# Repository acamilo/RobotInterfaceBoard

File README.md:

### Robot Interface Board

The Robot Interface Board (RIB) is a breakout board for the [ESP32-DevKitC Arduino module](https://www.digikey.com/product-detail/en/espressif-systems/ESP32-DEVKITC-32D-F/1965-1003-ND/9693290). The Dev Kit C is a reference design of the ESP32-WROOM-32 module which houses the WiFi and bluetooth Antenae. The ESP32-WROOM-32 module houses an ESP32 microcontroller. 

#### Datasheet

[Arduino compatiple DevkitC]( https://esp-idf.readthedocs.io/en/latest/get-started/get-started-devkitc.html)

[ESP32 Microcontroller]( https://www.espressif.com/sites/default/files/documentation/esp32_datasheet_en.pdf)

[ESP32-DevKitC Arduino module wireing diagram ](https://dl.espressif.com/dl/schematics/esp32_devkitc_v4-sch-20180607a.pdf)

## PCB

## ESP32Dev Board PINMAP

## IO Pin counts

There are 16 I/O pins availible for use in your programs with no external perpheral already using them.

There are 21 I/O pins availible for use in your programs including the 5 output only strapping pins.

There are 27 I/O pins availible for use in your programs by reusing the boot button pin, serial pins and i2c pins for other purposes. 

## User Button

There is a button connected to pin 0 and is accessible to the users code as a button. If you hold it whild pressing the reset button, however, it will hold the chip in bootloader mode and it will not run your code until the core is reset or programmed over the USB. Once your code starts, this button is availible for use as a button in your code and pressing it will not effect the opperation of the core after your program has started.  

## Pins to Never Use because they will disrupt programming and opperation:

6-11    - These pins are hookups for external system flash and are used by the system flash. Unless you are extending the chips flash capibilities, do not use these. 

1 and 3 -  these are used to program the device and are serial port pins.

## Output Only Pins 

These pins are strapping pins for the core, if pulled to a different state than the default not boot.

These are strapping pins and have to be in known states at the time of the chip booting. If you use them as outputs, be careful to note the the pull up or down resistor states for each. When using these pins make sure the weak-pull resistor will not interfeare with your intended opperation, and do not add additional weak-pull resistors.

```
2  (pull down)
5  (pull up)
12 (pull down)
13 (pull up)
15 (pull up)
```
## Input Only pins

34-39 are input only. They have no output modes at all. Analog input and digital input are availible.

```
35
34
39
36
```

## Availible as Both Input and Output

```
4
14
16-19
21-23
25-27
32-33
```
## External Use pins

0 is the boot pin, if held low during a reset it will prevent the device from booting

1 and 3 are the serial port used for programming and print statements. This should not be used for user functions, but can be used if serial functionality is needed.

13 Has an LED connected to it on the RIB

22 and 21 have 4.7kOhm pullups on them and are connected to the Wii accessory port. These can be used with other i2c devices.
See: https://github.com/acamilo/RobotInterfaceBoard/issues/31

27 Is connected to the Wii header as controller detect. When the controller is connected, this is pulled to 3.3v. It is open when the controller is not connected.  

## Availible Servo/PWM/AnalogWrite Pins

The ESP32 can generate up to 16 simultanious Servo signels. 

```
4     
5    
12-19 
21-23 
25-27 
32-33 
```

### Timer distribution for PWM
The ESP32 has 4 timers availible for use in PWM generation. All PWM channels using a given timer have the same base frequency. Changing the frequency of a channel will change the frequency of other channels. Note the chart for how the PWM channel allocations coorospond to timers:

```
/*
 * LEDC Chan to Group/Channel/Timer Mapping
** ledc: 0  => Group: 0, Channel: 0, Timer: 0
** ledc: 1  => Group: 0, Channel: 1, Timer: 0
** ledc: 2  => Group: 0, Channel: 2, Timer: 1
** ledc: 3  => Group: 0, Channel: 3, Timer: 1
** ledc: 4  => Group: 0, Channel: 4, Timer: 2
** ledc: 5  => Group: 0, Channel: 5, Timer: 2
** ledc: 6  => Group: 0, Channel: 6, Timer: 3
** ledc: 7  => Group: 0, Channel: 7, Timer: 3
** ledc: 8  => Group: 1, Channel: 0, Timer: 0
** ledc: 9  => Group: 1, Channel: 1, Timer: 0
** ledc: 10 => Group: 1, Channel: 2, Timer: 1
** ledc: 11 => Group: 1, Channel: 3, Timer: 1
** ledc: 12 => Group: 1, Channel: 4, Timer: 2
** ledc: 13 => Group: 1, Channel: 5, Timer: 2
** ledc: 14 => Group: 1, Channel: 6, Timer: 3
** ledc: 15 => Group: 1, Channel: 7, Timer: 3
*/
```

When using ESP32PWM objects, changing the frequency will check for timer cross-talk. If you re-set the frequency of a PWM indirectly, the object will print this warning:

```
	WARNING PWM channel 1 shares a timer with 0
	changing the frequency to 330.00 Hz will ALSO change channel 0 
	from its previous frequency of 50.00 Hz
```

If you get this warning you can space out the attach events of the hardware using ESP32PWM using dummy objects. To consume a channel without activating a pwm, you can add this to your code between attach method calls. 

```
ESP32PWM dummy;
dummy.getChannel();
```
## Availible DAC pins
```
25
26
```
These pins when used with analogWrite will produce an 8 bit analog value on the given pin. The value is from 0-3.3v mapped to 0-255 values. The api is to simply use analogWrite().

## Interrupt

For code examples: https://techtutorialsx.com/2017/09/30/esp32-arduino-external-interrupts/

Availible interruptable pins are all input pins.

# Development Computer Options  

## Option 1) A lab machine

Availible to all students. 

Note that the driver is installed on these computers

Note that Arduino with the ESP32 toolchain is already installed in C:\WPIAPPS\arduino-1.8.3\

Note Eclipse is installed on all workstations with the Sloeber plugin installed. 

##  Option 2) Personal Machine

### Supported for this class

Windows 10 Pro 

A user name with no " " in the file path. Generally it is safe to use your WPI username as the username on your computer.

Fresh install is genearlly reccomended every 6 months. Install disk are availible to students as a resource from the WPI Helpdesk.

OneDrive and Dropbox conflict with the install process and must be fully removed from the user file paths. 

Eclipse should be installed in 

```
C:/eclipse
```

Arduino should be installed in 

```
C:/RBE-arduino-install/
```

After installation of both, ensure your user has write access to the directories. 

### Unsupported OS's

MacOS is unsupported and only intermittantly working. Drivers have been an issue with programming our board, and virtualization of Windows within OSX is tested non-working. If you have Mac OSX please install a fresh copy of Windows 10 nativly and dual boot. 

Ubuntu 16.04 is unsupported but works well.

Ubuntu 18.04 is unsupported but works well with some creative directions following. This will take more effort and would require pre-existing proficency in Linux. If you have 18.04 please install Windows 10 or 16.04. 

### How to get Windows 10 as a Student for free from WPI

To get your student copy of Windows go here: 

https://onlinestore.wpi.edu/

Select windows 10, and download it. For students you get one copy and it is free. 

You can follow this tutorial to install it:

https://www.youtube.com/watch?v=aTVOTY93XXU

# Arduino and the ESP32 Toolchain

This is installed on the lab machines already. 

After extracting the Zip file, install the 64 bit version of the driver. 

https://www.silabs.com/products/development-tools/software/usb-to-uart-bridge-vcp-drivers

Arduino IDE download :

https://github.com/WPIRoboticsEngineering/RobotInterfaceBoard/releases/download/rev5-1/RBE-arduino110718.zip

And extract it on your computer in 

```
C:/RBE-arduino-install/
```

Make a sketchbook folder in C:/, or (R:/ on the lab machines) make a folder:

```
C:/RBEArduino/
```

Make sure it is user level read-write

Run Arduino in the extracted folder.

Open the Preferences in Arduino and set the Sketchbook location to:

```
C:/RBEArduino/
```
Use [Arduino IDE and Github Desktop](https://github.com/WPIRoboticsEngineering/RobotInterfaceBoard/blob/master/UseArduinoGithubDesktop.md)

After your Arduino is installed and the ESP32 toolchain is up and running, open Arduino IDE and Select your board:

```
Tools->Board->ESP32 Dev Module
```

And select your port:

```
Tools->Port-> (the port that your arduino is connected to)
```

## Personal Computer install Linux / Mac  (Unsupported)

Ubuntu 18.04 Instructions:

[InstallToolchainOnUbuntu18-04.md](InstallToolchainOnUbuntu18-04.md)

Ubuntu 16.04 Instructions:

https://github.com/espressif/arduino-esp32/blob/master/docs/arduino-ide/debian_ubuntu.md

Mac instructions (NOT SUPPORTED BY RBE, HAS LOTS OF PROBLEMS):

https://github.com/espressif/arduino-esp32/blob/master/docs/arduino-ide/mac.md

## Install Eclipse And Setup Eclipse on Personal Machine

 [See Eclipse install instructions in InstallEclipse.md](https://github.com/WPIRoboticsEngineering/RobotInterfaceBoard/blob/master/InstallEclipse.md)
 
 [Open Projects in Eclipse using the Eclipse instructions](https://github.com/WPIRoboticsEngineering/RobotInterfaceBoard/blob/master/UseEclipse.md)

# Arduino Libraries
## HOWTO
For detailed instructions on how libraries work, see: https://www.arduino.cc/en/Guide/Libraries

Open Arduino and select Sketch->Libraries -> Manage Libraries
## Which Libraries

### 1001

ESP32Servo

ESP32Encoder

### 2001
Search for and install:

ESP32Servo

ESP32Encoder

Esp32SimplePacketComs

SimplePacketComs

### 2002
Search for and install:

ESP32Servo

ESP32Encoder

Adafruit_BNO055

Adafruit Unified Sensor

Esp32SimplePacketComs

SimplePacketComs

DFRobotIRPosition

# FAQ and troubleshooting

### "I dont see 'ESP32 Dev Module' as an option in Arduino when I try to select my board..."

* Use a lab machine. This will not be a problem on the lab machines. 

* You need to install the ESP 32 toolchain. See https://github.com/WPIRoboticsEngineering/RobotInterfaceBoard#personal-computer-install-windows--supported

### "I can compile the code but I do not have a serial port option in Arduino..."

* Ensure the driver installed https://github.com/WPIRoboticsEngineering/RobotInterfaceBoard#personal-computer-install-windows--supported

* If its a MAC, this is the issue that causes us to say MacOS is UNSUPPORTED. Install Windows https://github.com/WPIRoboticsEngineering/RobotInterfaceBoard#how-to-get-windows-10-as-a-student-for-free-from-wpi

* Make sure the USB Micro cable is a data cable, not just a crappy USB charging cable with no data lines. 

### "I can select the correct serial port, put it wont program or times out while programming..."

* Program an example script using Lab computer   (if this works have them re-download the pre-packaged arduino from https://github.com/WPIRoboticsEngineering/RobotInterfaceBoard#personal-computer-install-windows--supported ) 

* Is the serial moniter open? Close it and try again. 

* Did it program earlier? Unplug the USB and plug it back in.

* Hold Boot button and Strobe the enable button to set core into bootloader mode. Try to program. (If this helps, you are printing too much data to the serial port)

* Unplug everything from all IO (If this fixes it, check the pins and voltages, also check for diode dead-shorts check https://github.com/WPIRoboticsEngineering/RobotInterfaceBoard#pins-to-never-use )

* Check to see if the processor or regulator is HOT. If it is, a dead-short or over-voltage event occured and the device is dead forever. Replace. 

### "I can program it but it but it keeps rebooting over and over..."

* Null pointers are the #1 cause of this behavior, use print statements to isolate the point where it reboots and check for null pointers. This is the issue 9 out of 10 times. 

* Interrupt issues - Interrupts that access memory that is used by non-interrupt code without a mutex or semiphore. Try disabling the interrupt and if this fixed the reboot issue, then go ahead and implement the mutex locking. 

* Something may also be plugged into one of the off-limits pins, or your code is reconfiguring and messing up one of these pins. See: https://github.com/WPIRoboticsEngineering/RobotInterfaceBoard#pins-to-never-use 

### "This processor seems more complicated than the Uno and the Mega, why are we using it?"

* The ESP32 is a faster core at 260Mhz, vs the 16Mhz Uno. It is also dual-core.

* It has more perpherals needed for building robots, 16x 12 bit ADC, 2x DAC and 16 hardware encoder perpherals

* It has hardware and software that support WiFi for communications. 

* 32 bit processing with an FPU means complex math is possible on the microcontroller. 

* It is Arduino compatible for programming and Library support

* It is an open source design of the DevKit-C module, using an open source MIPS core and open soruce tool-chain

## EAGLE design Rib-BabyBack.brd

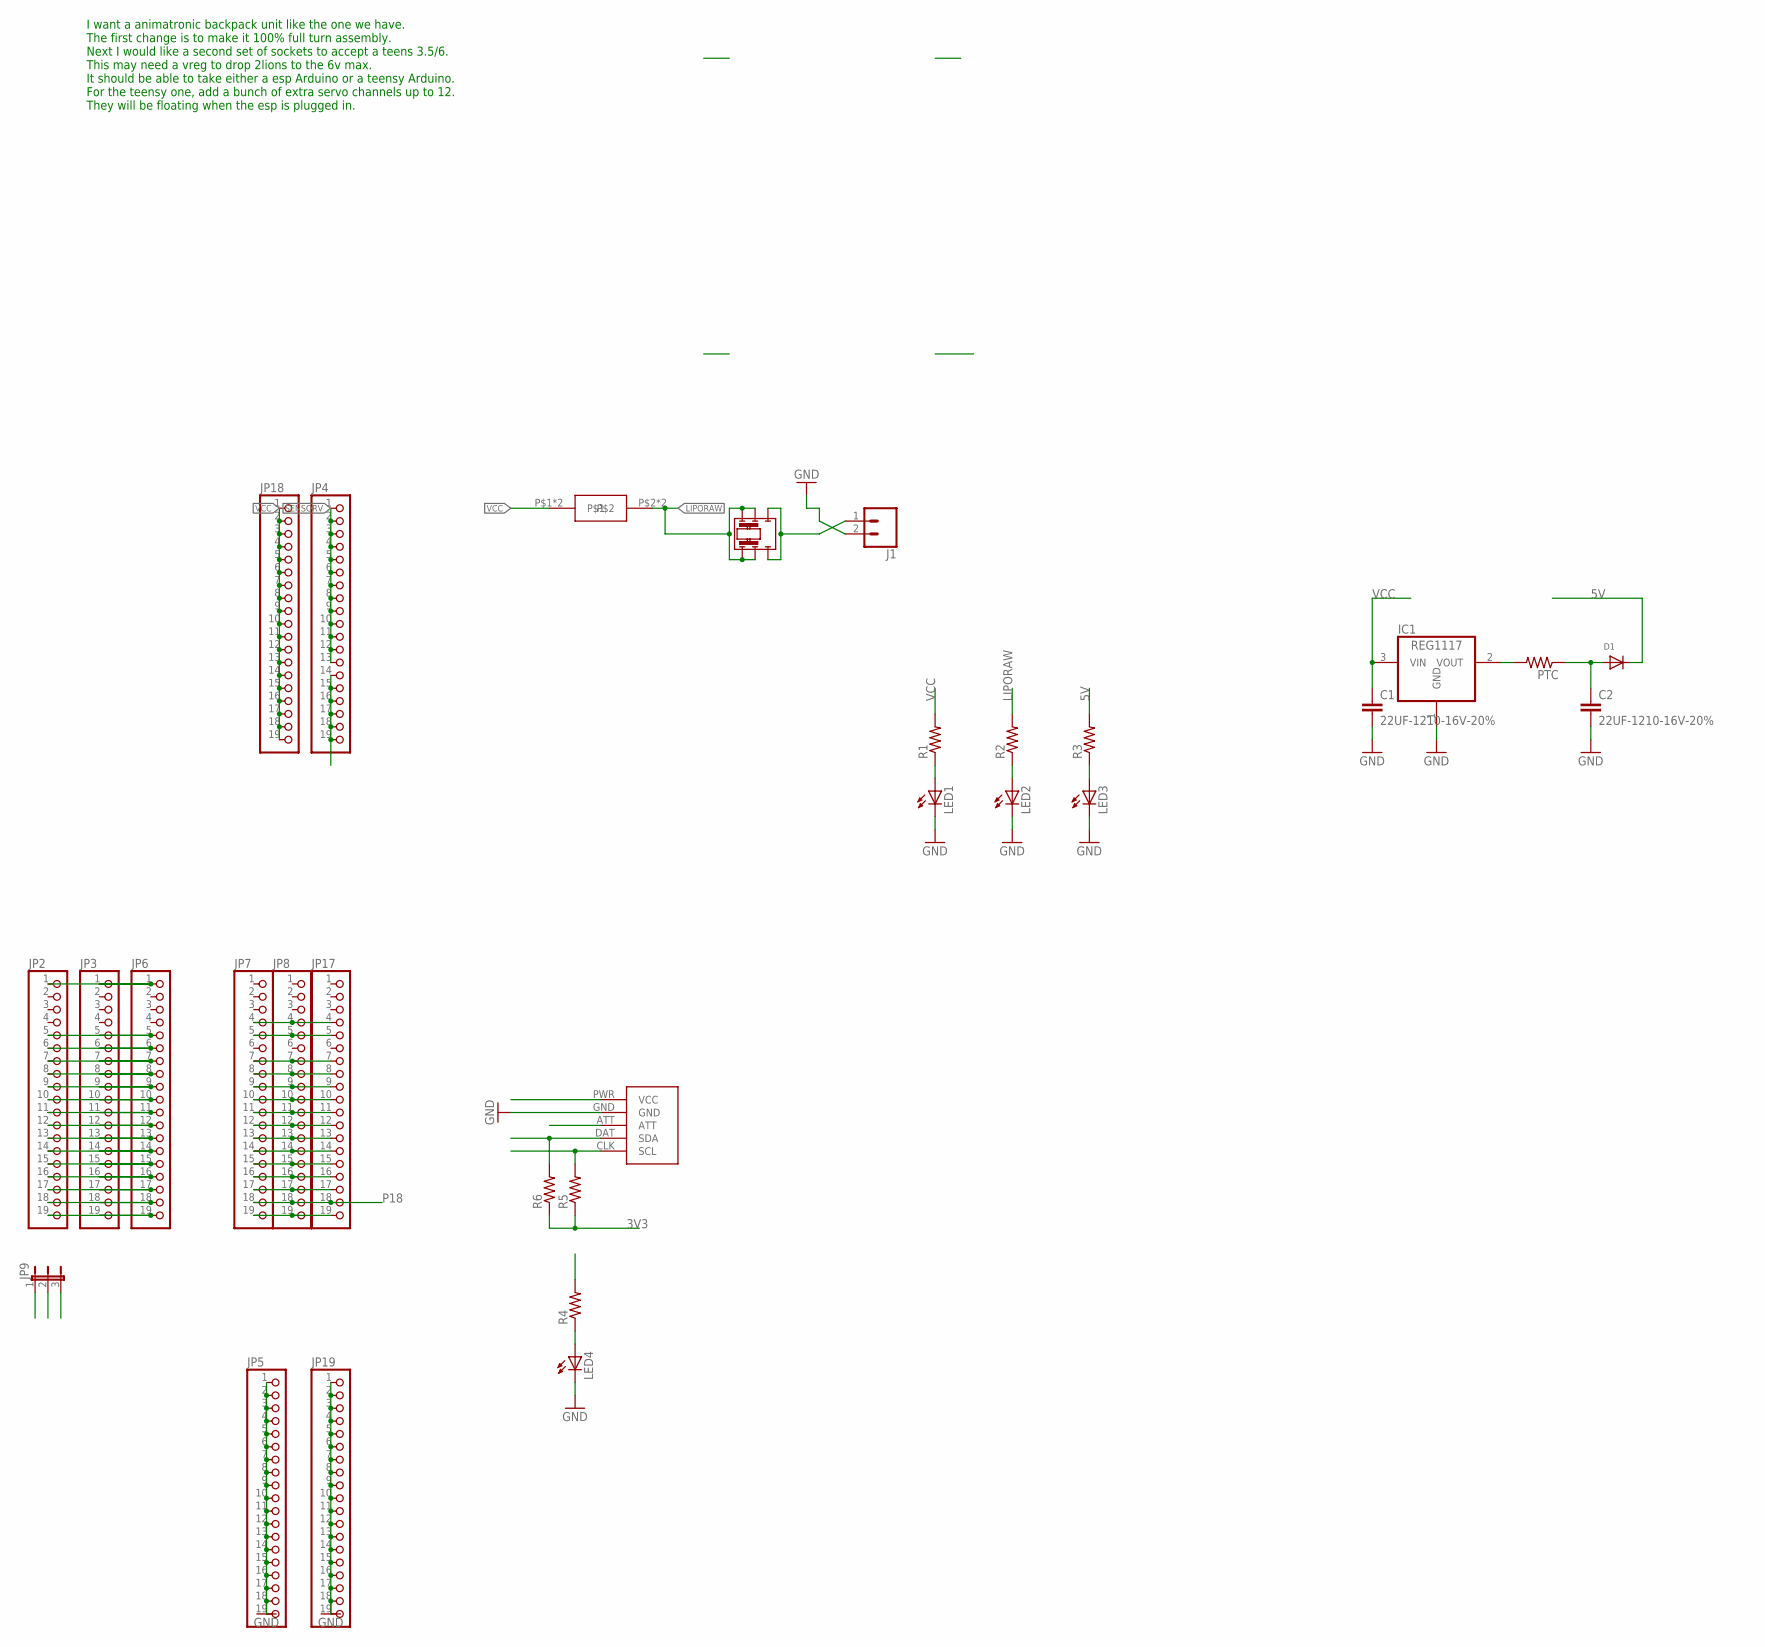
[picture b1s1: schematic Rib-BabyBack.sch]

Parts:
C1, C2: 22UF-1210-16V-20%; 1210
D1: DIODESOD-523; SOD-523
F4: 3557-2
IC1: REG1117; SOT223
J1: CONN_023.5MM_LOCK; SCREWTERMINAL-3.5MM-2_LOCK
JP2, JP3, JP4, JP5, JP6, JP7, JP8, JP17, JP18, JP19: PINHD-1X19; 1X19
JP9: JP2E; JP2
LED1, LED2, LED3, LED4: LED_ESML0603; LED_SML0603
PTC: R-US_R0805; R0805
R1, R2, R3, R4, R5, R6: R-US_R0603; R0603
SW1: DPDT; GF-126-0327
U$5: WIICHUCK; CHUCK

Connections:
3V3: JP2.19, JP3.19, JP6.19, JP9.1, R5.1, R6.1, U$5.PWR (VCC)
DET: JP2.9, JP3.9, JP6.9, U$5.ATT
GND: C1.2, C2.2, IC1.1 (GND), J1.2, JP2.6, JP3.6, JP5.1, JP5.2, JP5.3, JP5.4, JP5.5, JP5.6, JP5.7, JP5.8, JP5.9, JP5.10, JP5.11, JP5.12, JP5.13, JP5.14, JP5.15, JP5.16, JP5.17, JP5.18, JP5.19, JP6.6, JP7.13, JP7.19, JP8.13, JP8.19, JP17.13, JP17.19, JP19.1, JP19.2, JP19.3, JP19.4, JP19.5, JP19.6, JP19.7, JP19.8, JP19.9, JP19.10, JP19.11, JP19.12, JP19.13, JP19.14, JP19.15, JP19.16, JP19.17, JP19.18, JP19.19, LED1.C, LED2.C, LED3.C, LED4.C, U$5.GND
LIPORAW: F4.P$2, F4.P$3, R2.2, SW1.A1, SW1.A2, SW1.B1, SW1.B2
unnamed: LED4.A, R4.1
unnamed: C2.1, D1.A, PTC.1
unnamed: IC1.2 (VOUT), PTC.2
unnamed: J1.1, SW1.C1, SW1.C2
unnamed: JP2.7, JP3.7, JP6.7
unnamed: JP2.8, JP3.8, JP6.8
unnamed: JP2.10, JP3.10, JP6.10
unnamed: JP2.11, JP3.11, JP6.11
unnamed: JP2.12, JP3.12, JP6.12
unnamed: JP2.13, JP3.13, JP6.13
unnamed: JP2.14, JP3.14, JP6.14
unnamed: JP2.15, JP3.15, JP6.15
unnamed: JP2.16, JP3.16, JP6.16
unnamed: JP2.17, JP3.17, JP6.17
unnamed: JP2.18, JP3.18, JP6.18
unnamed: LED1.A, R1.1
unnamed: JP7.4, JP8.4, JP17.4
unnamed: JP7.5, JP8.5, JP17.5
unnamed: JP7.7, JP8.7, JP17.7
unnamed: JP7.8, JP8.8, JP17.8
unnamed: JP7.9, JP8.9, JP17.9
unnamed: JP7.10, JP8.10, JP17.10
unnamed: JP7.11, JP8.11, JP17.11
unnamed: JP7.12, JP8.12, JP17.12
unnamed: LED2.A, R2.1
unnamed: LED3.A, R3.1
P13: JP2.5, JP3.5, JP6.5, R4.2
P18: JP7.18, JP8.18, JP17.18
RX0: JP7.15, JP8.15, JP17.15
SCL: JP7.17, JP8.17, JP17.17, R5.2, U$5.CLK (SCL)
SDA: JP7.14, JP8.14, JP17.14, R6.2, U$5.DAT (SDA)
TX0: JP7.16, JP8.16, JP17.16
VCC: C1.1, F4.P$1, F4.P$4, IC1.3 (VIN), JP18.1, JP18.2, JP18.3, JP18.4, JP18.5, JP18.6, JP18.7, JP18.8, JP18.9, JP18.10, JP18.11, JP18.12, JP18.13, JP18.14, JP18.15, JP18.16, JP18.17, JP18.18, JP18.19, R1.2

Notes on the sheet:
I want a animatronic backpack unit like the one we have. The first change is to make it 100% full turn assembly. Next I would like a second set of sockets to accept a teens 3.5/6. This may need a vreg to drop 2lions to the 6v max. It should be able to take either a esp Arduino or a teensy Arduino. 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

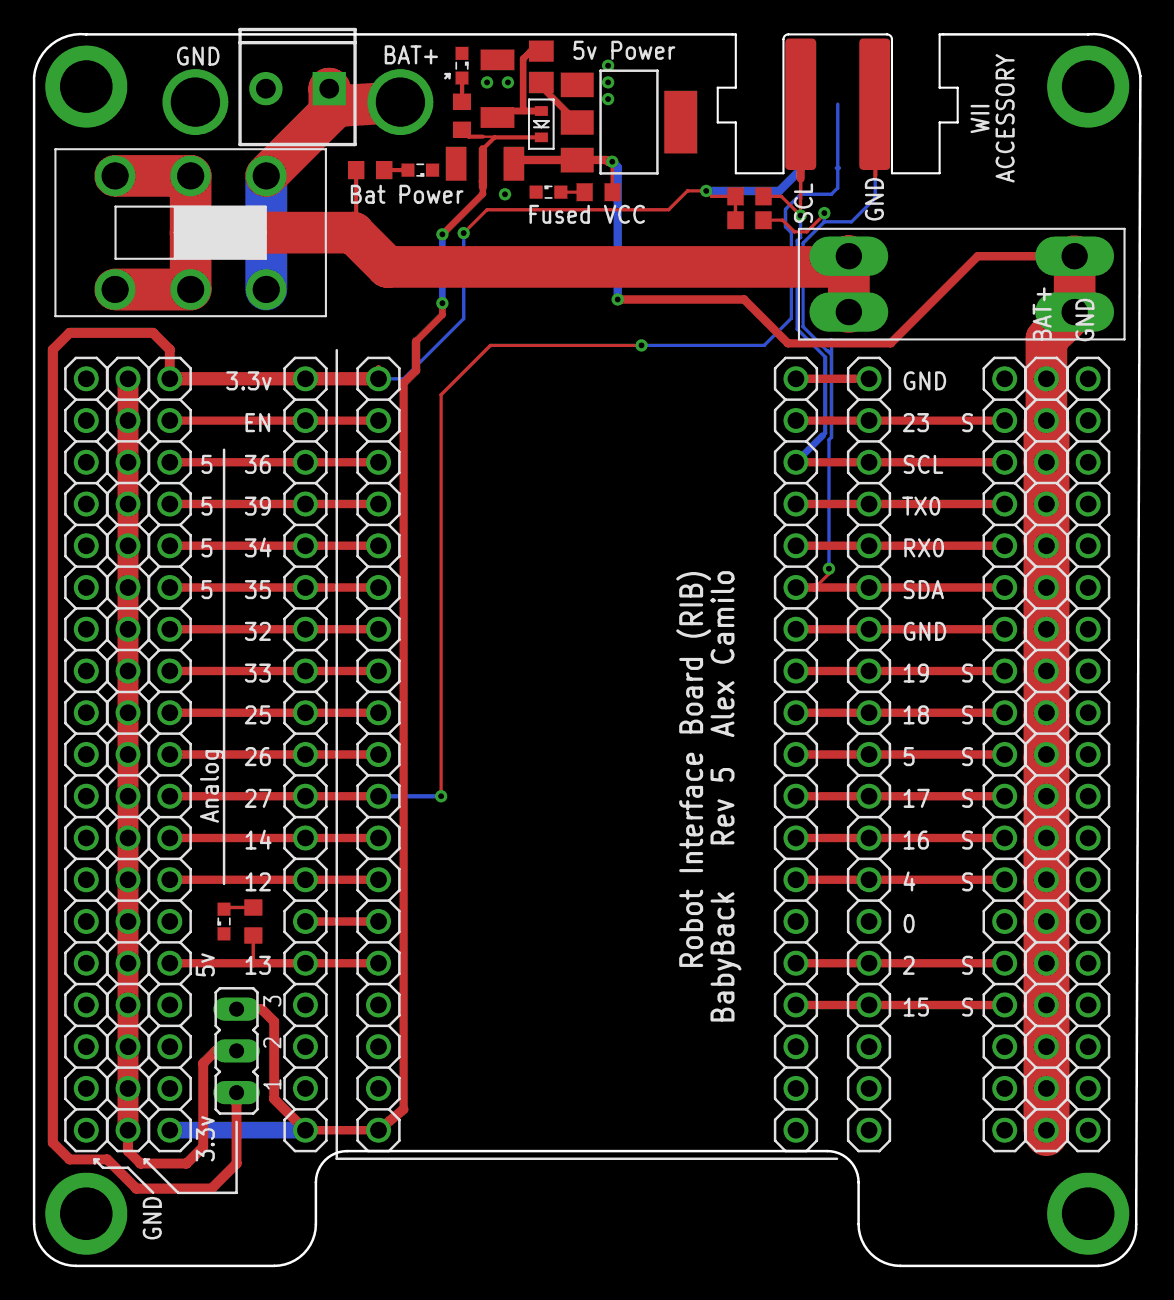
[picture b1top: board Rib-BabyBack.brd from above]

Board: 2 copper layers, 67.3 x 74.9 mm, 30 parts (0 on the bottom side), 39 nets.

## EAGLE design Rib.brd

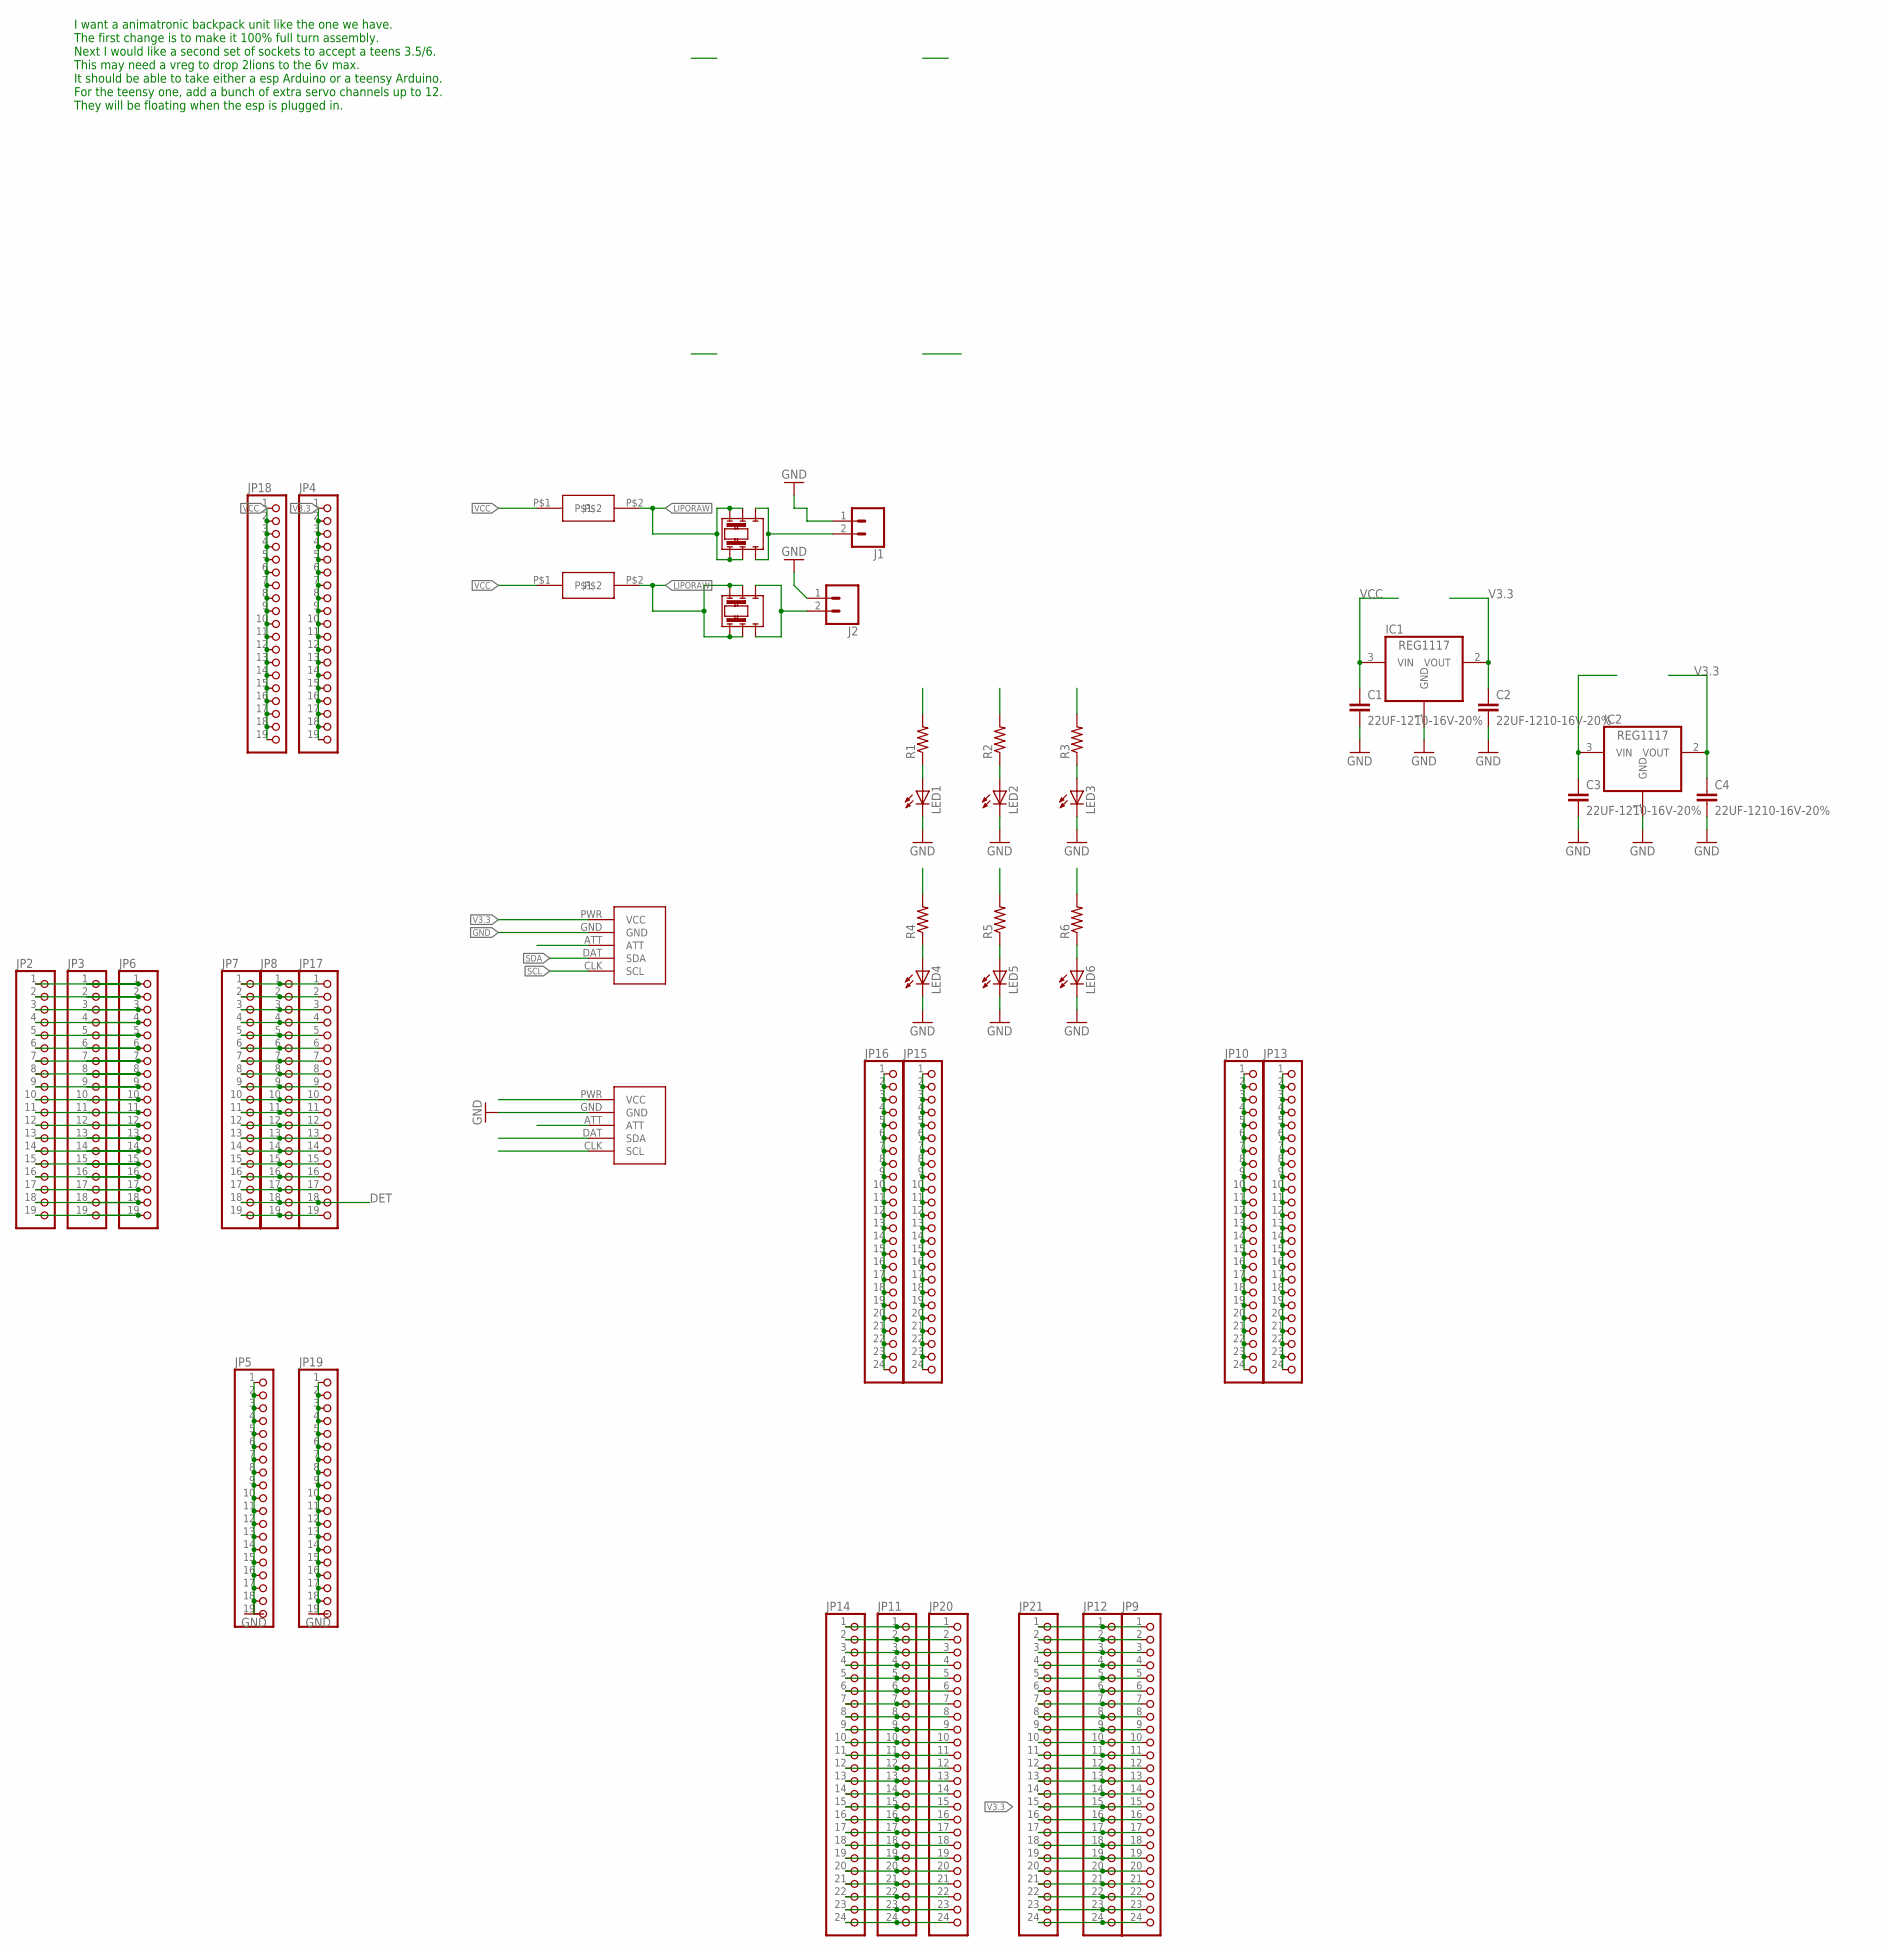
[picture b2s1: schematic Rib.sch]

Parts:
C1, C2, C3, C4: 22UF-1210-16V-20%; 1210
F3, F4: 3557-2
IC1, IC2: REG1117; SOT223
J1, J2: CONN_023.5MM_LOCK; SCREWTERMINAL-3.5MM-2_LOCK
JP2, JP3, JP4, JP5, JP6, JP7, JP8, JP17, JP18, JP19: PINHD-1X19; 1X19
JP9, JP10, JP11, JP12, JP13, JP14, JP15, JP16, JP20, JP21: PINHD-1X24; 1X24
LED1, LED2, LED3, LED4, LED5, LED6: LED_ESML0603; LED_SML0603
R1, R2, R3, R4, R5, R6: R-US_R0603; R0603
SW1, SW2: DPDT; GF-126-0327
U$3, U$5: WIICHUCK; CHUCK

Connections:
5V: JP2.1, JP3.1, JP6.1, JP11.1, JP14.1, JP20.1
DET: JP7.18, JP8.18, JP9.24, JP12.24, JP17.18, JP21.24, U$3.ATT, U$5.ATT
GND: C1.2, C2.2, C3.2, C4.2, IC1.1 (GND), IC2.1 (GND), J1.1, J2.1, JP2.6, JP3.6, JP5.1, JP5.2, JP5.3, JP5.4, JP5.5, JP5.6, JP5.7, JP5.8, JP5.9, JP5.10, JP5.11, JP5.12, JP5.13, JP5.14, JP5.15, JP5.16, JP5.17, JP5.18, JP5.19, JP6.6, JP7.13, JP7.19, JP8.13, JP8.19, JP9.1, JP11.2, JP11.15, JP12.1, JP13.1, JP13.2, JP13.3, JP13.4, JP13.5, JP13.6, JP13.7, JP13.8, JP13.9, JP13.10, JP13.11, JP13.12, JP13.13, JP13.14, JP13.15, JP13.16, JP13.17, JP13.18, JP13.19, JP13.20, JP13.21, JP13.22, JP13.23, JP13.24, JP14.2, JP14.15, JP16.1, JP16.2, JP16.3, JP16.4, JP16.5, JP16.6, JP16.7, JP16.8, JP16.9, JP16.10, JP16.11, JP16.12, JP16.13, JP16.14, JP16.15, JP16.16, JP16.17, JP16.18, JP16.19, JP16.20, JP16.21, JP16.22, JP16.23, JP16.24, JP17.13, JP17.19, JP19.1, JP19.2, JP19.3, JP19.4, JP19.5, JP19.6, JP19.7, JP19.8, JP19.9, JP19.10, JP19.11, JP19.12, JP19.13, JP19.14, JP19.15, JP19.16, JP19.17, JP19.18, JP19.19, JP20.2, JP20.15, JP21.1, LED1.C, LED2.C, LED3.C, LED4.C, LED5.C, LED6.C, U$3.GND, U$5.GND
LIPORAW: F3.P$2, F4.P$2, R2.2, R5.2, SW1.A1, SW1.A2, SW1.B1, SW1.B2, SW2.A1, SW2.A2, SW2.B1, SW2.B2
unnamed: JP11.23, JP14.23, JP20.23
unnamed: JP11.24, JP14.24, JP20.24
unnamed: JP2.2, JP3.2, JP6.2
unnamed: JP2.3, JP3.3, JP6.3
unnamed: JP2.4, JP3.4, JP6.4
unnamed: JP2.5, JP3.5, JP6.5
unnamed: J1.2, SW1.C1, SW1.C2
unnamed: JP2.7, JP3.7, JP6.7
unnamed: JP2.8, JP3.8, JP6.8
unnamed: JP2.9, JP3.9, JP6.9
unnamed: JP2.10, JP3.10, JP6.10
unnamed: JP2.11, JP3.11, JP6.11
unnamed: JP2.12, JP3.12, JP6.12
unnamed: JP2.13, JP3.13, JP6.13
unnamed: JP2.14, JP3.14, JP6.14
unnamed: JP2.15, JP3.15, JP6.15
unnamed: JP2.16, JP3.16, JP6.16
unnamed: JP2.17, JP3.17, JP6.17
unnamed: JP2.18, JP3.18, JP6.18
unnamed: LED1.A, R1.1
unnamed: JP7.1, JP8.1, JP17.1
unnamed: JP7.2, JP8.2, JP17.2
unnamed: JP7.3, JP8.3, JP17.3
unnamed: JP7.4, JP8.4, JP17.4
unnamed: JP7.5, JP8.5, JP17.5
unnamed: JP7.6, JP8.6, JP17.6
unnamed: JP7.7, JP8.7, JP17.7
unnamed: JP7.8, JP8.8, JP17.8
unnamed: JP7.9, JP8.9, JP17.9
unnamed: JP7.10, JP8.10, JP17.10
unnamed: JP7.11, JP8.11, JP17.11
unnamed: JP7.12, JP8.12, JP17.12
unnamed: LED2.A, R2.1
unnamed: LED3.A, R3.1
unnamed: J2.2, SW2.C1, SW2.C2
unnamed: LED4.A, R4.1
unnamed: LED5.A, R5.1
unnamed: LED6.A, R6.1
unnamed: JP11.3, JP14.3, JP20.3
unnamed: JP11.4, JP14.4, JP20.4
unnamed: JP11.5, JP14.5, JP20.5
unnamed: JP11.6, JP14.6, JP20.6
unnamed: JP11.7, JP14.7, JP20.7
unnamed: JP11.10, JP14.10, JP20.10
unnamed: JP11.11, JP14.11, JP20.11
unnamed: JP11.12, JP14.12, JP20.12
unnamed: JP11.13, JP14.13, JP20.13
unnamed: JP11.14, JP14.14, JP20.14
unnamed: JP11.16, JP14.16, JP20.16
unnamed: JP11.17, JP14.17, JP20.17
unnamed: JP11.18, JP14.18, JP20.18
unnamed: JP11.19, JP14.19, JP20.19
unnamed: JP11.20, JP14.20, JP20.20
unnamed: JP11.21, JP14.21, JP20.21
unnamed: JP11.22, JP14.22, JP20.22
unnamed: JP9.2, JP12.2, JP21.2
unnamed: JP9.3, JP12.3, JP21.3
unnamed: JP9.4, JP12.4, JP21.4
unnamed: JP9.5, JP12.5, JP21.5
unnamed: JP9.6, JP12.6, JP21.6
unnamed: JP9.7, JP12.7, JP21.7
unnamed: JP9.8, JP12.8, JP21.8
unnamed: JP9.9, JP12.9, JP21.9
unnamed: JP9.10, JP12.10, JP21.10
unnamed: JP9.13, JP12.13, JP21.13
unnamed: JP9.14, JP12.14, JP21.14
unnamed: JP9.16, JP12.16, JP21.16
unnamed: JP9.17, JP12.17, JP21.17
unnamed: JP9.18, JP12.18, JP21.18
unnamed: JP9.19, JP12.19, JP21.19
unnamed: JP9.20, JP12.20, JP21.20
unnamed: JP9.21, JP12.21, JP21.21
unnamed: JP9.22, JP12.22, JP21.22
unnamed: JP9.23, JP12.23, JP21.23
RX0: JP7.15, JP8.15, JP9.12, JP12.12, JP17.15, JP21.12
SCL: JP7.17, JP8.17, JP11.8, JP14.8, JP17.17, JP20.8, U$3.CLK (SCL), U$5.CLK (SCL)
SDA: JP7.14, JP8.14, JP11.9, JP14.9, JP17.14, JP20.9, U$3.DAT (SDA), U$5.DAT (SDA)
TX0: JP7.16, JP8.16, JP9.11, JP12.11, JP17.16, JP21.11
V3.3: C2.1, C4.1, IC1.2 (VOUT), IC2.2 (VOUT), JP2.19, JP3.19, JP4.1, JP4.2, JP4.3, JP4.4, JP4.5, JP4.6, JP4.7, JP4.8, JP4.9, JP4.10, JP4.11, JP4.12, JP4.13, JP4.14, JP4.15, JP4.16, JP4.17, JP4.18, JP4.19, JP6.19, JP9.15, JP10.1, JP10.2, JP10.3, JP10.4, JP10.5, JP10.6, JP10.7, JP10.8, JP10.9, JP10.10, JP10.11, JP10.12, JP10.13, JP10.14, JP10.15, JP10.16, JP10.17, JP10.18, JP10.19, JP10.20, JP10.21, JP10.22, JP10.23, JP10.24, JP12.15, JP21.15, R3.2, R6.2, U$3.PWR (VCC), U$5.PWR (VCC)
VCC: C1.1, C3.1, F3.P$1, F4.P$1, IC1.3 (VIN), IC2.3 (VIN), JP15.1, JP15.2, JP15.3, JP15.4, JP15.5, JP15.6, JP15.7, JP15.8, JP15.9, JP15.10, JP15.11, JP15.12, JP15.13, JP15.14, JP15.15, JP15.16, JP15.17, JP15.18, JP15.19, JP15.20, JP15.21, JP15.22, JP15.23, JP15.24, JP18.1, JP18.2, JP18.3, JP18.4, JP18.5, JP18.6, JP18.7, JP18.8, JP18.9, JP18.10, JP18.11, JP18.12, JP18.13, JP18.14, JP18.15, JP18.16, JP18.17, JP18.18, JP18.19, R1.2, R4.2

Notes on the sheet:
I want a animatronic backpack unit like the one we have. The first change is to make it 100% full turn assembly. Next I would like a second set of sockets to accept a teens 3.5/6. This may need a vreg to drop 2lions to the 6v max. It should be able to take either a esp Arduino or a teensy Arduino. 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

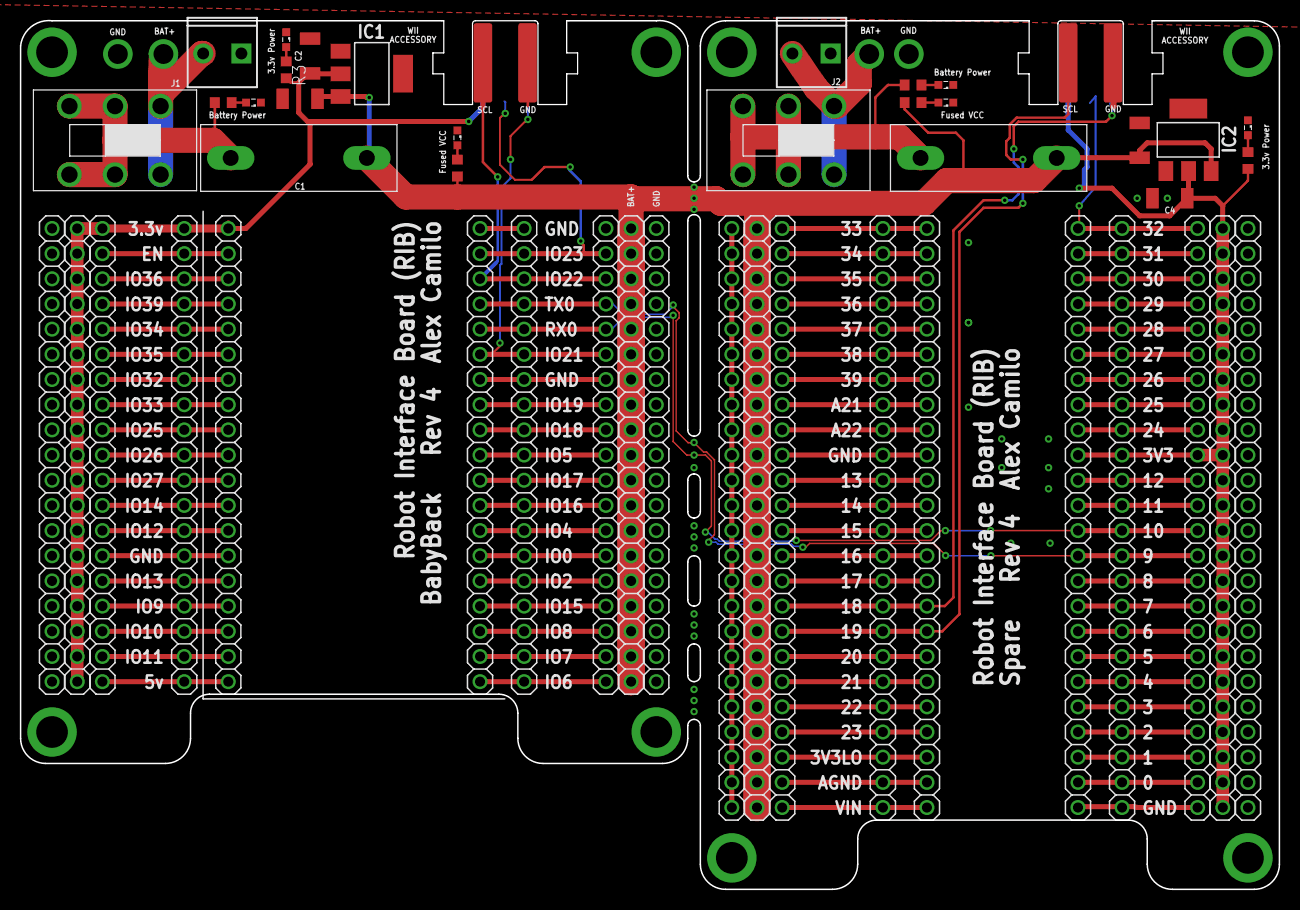
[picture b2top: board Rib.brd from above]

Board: 2 copper layers, 127.0 x 87.6 mm, 46 parts (0 on the bottom side), 84 nets.

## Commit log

2017-11-30 Rev 3 commit
2018-02-15 Updated Locking connecter library footprint with more clearence for locking pins
2018-02-15 Updated PCB footprints with updated wiichuck footprint
2018-02-15 Replaced JST power connectors with screw terminals
2018-02-15 Moved teensy power connector and added solder lugs for a cable to both boards
2018-02-15 ESP32 SDA now on pin 21
2018-02-27 label wii connector pins
2018-02-27 label Power and GND on battery connection
2018-02-27 DET pins routed to esp and teensy
2018-02-27 upped rev no to 4
2018-03-02 BOM and Centroid added
2018-03-02 Gerbers added
2018-03-02 DK parts for all lines
2018-03-22 Replaced fuseholder with blade style automotive fuse
2018-03-22 Added Power, Fuse, Regulated satus LEDs
2018-04-04 #28 Adding a readme
2018-04-04 Adding image
2018-04-12 Issue #35: Split esp32 board off into its own file
2018-04-12 Issue #26 Disconnect specific IO used by System Resources on ESP32
2018-04-12 Issue #32 ESP32 needs a user accessible LED on 13
2018-04-12 Issue #22 Solder lugs resized to 3MM diameter holes and moved
2018-04-12 Issue #19 4k7 ohm pullups to 3.3v are needed on SDA and SCL
2018-04-13 Issue #18 Fix footprint for fuse holder
2018-04-13 Issue #21 Added a pad for a PTC resetabble fuse for the 3.3v rail
2018-04-13 Issues #33 and 4 and #36
2018-04-13 Issue #34
2018-04-20 Resolved issue 37
2018-04-20 Resolved issue 38
2018-04-20 Resolved issue 31
2018-04-26 Resolved issue #24
2018-04-26 Resolved issue #23
2018-04-30 Resolved issue #27
2018-04-30 added board image and readme. #28
2018-04-30 Moving images into folder
2018-05-03 Moved fuse holder as per #40
2018-05-03 Updated silkscreen indicating analog pins #41
2018-05-03 updated board render to reflect new fuse location
2018-05-07 Updated BOM. #20 #25
2018-05-07 Removed binaries
2018-06-06 added missing fuse and diode to BOM
2018-07-16 changed 5v rail
2018-07-16 Removed Extra folder
2018-07-16 Fixed R1-4 in bom
2018-08-02 Updated centroid to include surface mount and through hole compnents
2018-08-02 added JP9 to BOM
2018-09-24 docs initial commit
2019-01-11 adding setup docs to board readme
2019-01-11 moved teh doc to docs
2019-02-01 Add 18.04 instructions
2019-02-01 Fix instructions link
2019-03-27 highlight the button to press
2019-03-27 Create setESPConfigs.png
    Adding espconfig
2019-06-19 Added polulu DC-DC
2019-06-19 added devkit PCB
2019-06-19 Added headers
2019-06-19 power jumpers for rails.
2019-06-19 Add rail fuse and fuse indicators
2019-06-24 add temp files to gitignore
2019-06-24 i2c circuit
2019-06-24 Update Ribv6.sch
    Added level hifting for 19,18,17,16,25,14
2019-06-24 Added indicator LEDS
2019-06-24 Battery Connector
2019-06-24 Extra header to accomidate shorter modules
2019-06-25 Update Ribv6.sch
    Added connectors for 5v
    removed extra header.
2019-07-02 Fuse FP
2019-07-02 Wii conn FP
2019-07-02 bananna FP
2019-07-02 added new features to sch
2019-07-02 first iter of PCB
2019-07-02 Removed eagle BRD
2019-07-02 fewer i2c conns in schematic
2019-07-08 routing draft
2019-07-08 layout done, partial silk
2019-10-16 Added lib for switch.
2019-10-16 re-laying out power section.
2019-10-18 Update polulu-3784-D36V28F7.kicad_mod
    Changed top rigt hole to recieve solderable standoff.
2019-10-21 more routing
2019-10-22 finished routing.
2019-10-22 Added LED on pin 13
    #6
2020-01-17 Board Updates.
    #3 Updated power system for the rib
    * Bolt holes on a 5.5mm grid
    * Second ehader added so narrow ESP32 devkit can be used
    * Accepts a 7.5 to 18v battery with solder lugs and bannana plugs
    * 5v 2 amp REG for esp32
    * 2 external power converter ports
2020-01-17 Added labels to power lugs, Bannana jacks #12
    Added labels to power lugs, Bannana jacks #12

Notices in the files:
parts and their libraries:
SparkFun-Capacitors: Licensing: Creative Commons ShareAlike 4.0 International - https://creativecommons.org/licenses/by-sa/4.0
